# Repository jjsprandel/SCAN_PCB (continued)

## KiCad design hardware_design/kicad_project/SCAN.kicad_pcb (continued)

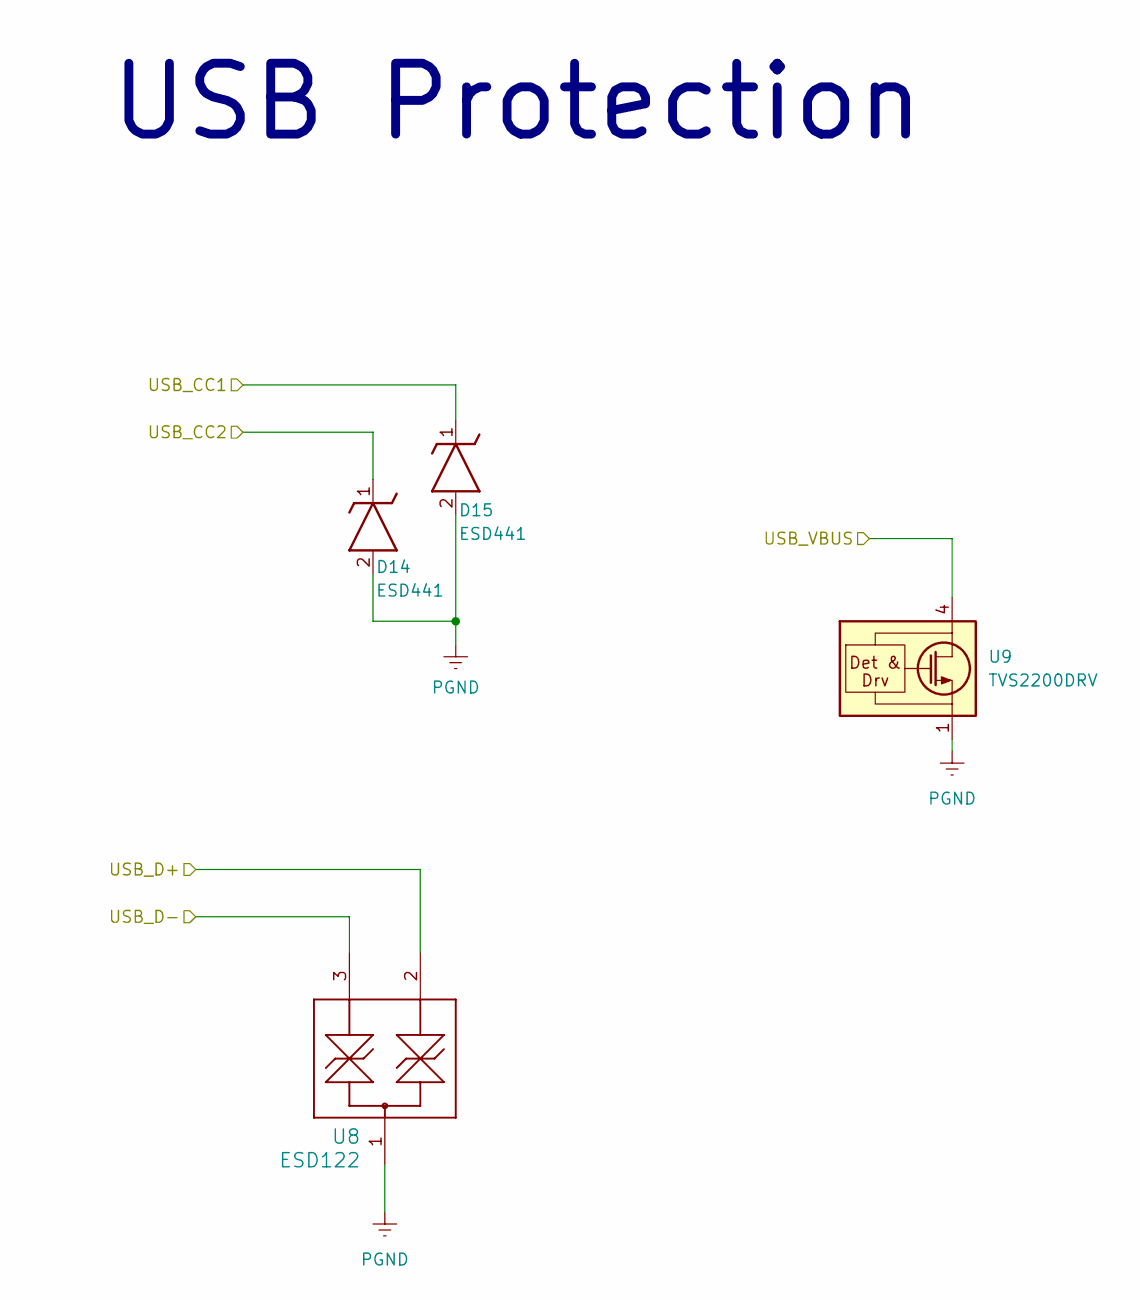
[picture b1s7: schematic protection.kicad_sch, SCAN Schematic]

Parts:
D14, D15: ESD441; X2SON2_DPL_TEX; Manufacturer_Part_Number ESD441DPLR; JLCPCB Part Number C22427765
U8: ESD122; DMY0003A; MFR_PN ESD122DMYR; JLCPCB Part Number C1975871
U9: TVS2200DRV; WSON-6-1EP_2x2mm_P0.65mm_EP1x1.6mm; MFR_PN TVS2200DRVR; JLCPCB Part Number C523793

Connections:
/USB_CC1: D15.1; also elsewhere on the board
/USB_CC2: D14.1; also elsewhere on the board
/USB_D+: U8.2; also elsewhere on the board
/USB_D-: U8.3; also elsewhere on the board
/USB_VBUS: U9.4 (IN), U9.5 (IN), U9.6 (IN); also elsewhere on the board
PGND: D14.2, D15.2, U8.1, U9.1 (GND), U9.2 (GND), U9.3 (GND), U9.7 (GND); also elsewhere on the board

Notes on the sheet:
USB Protection

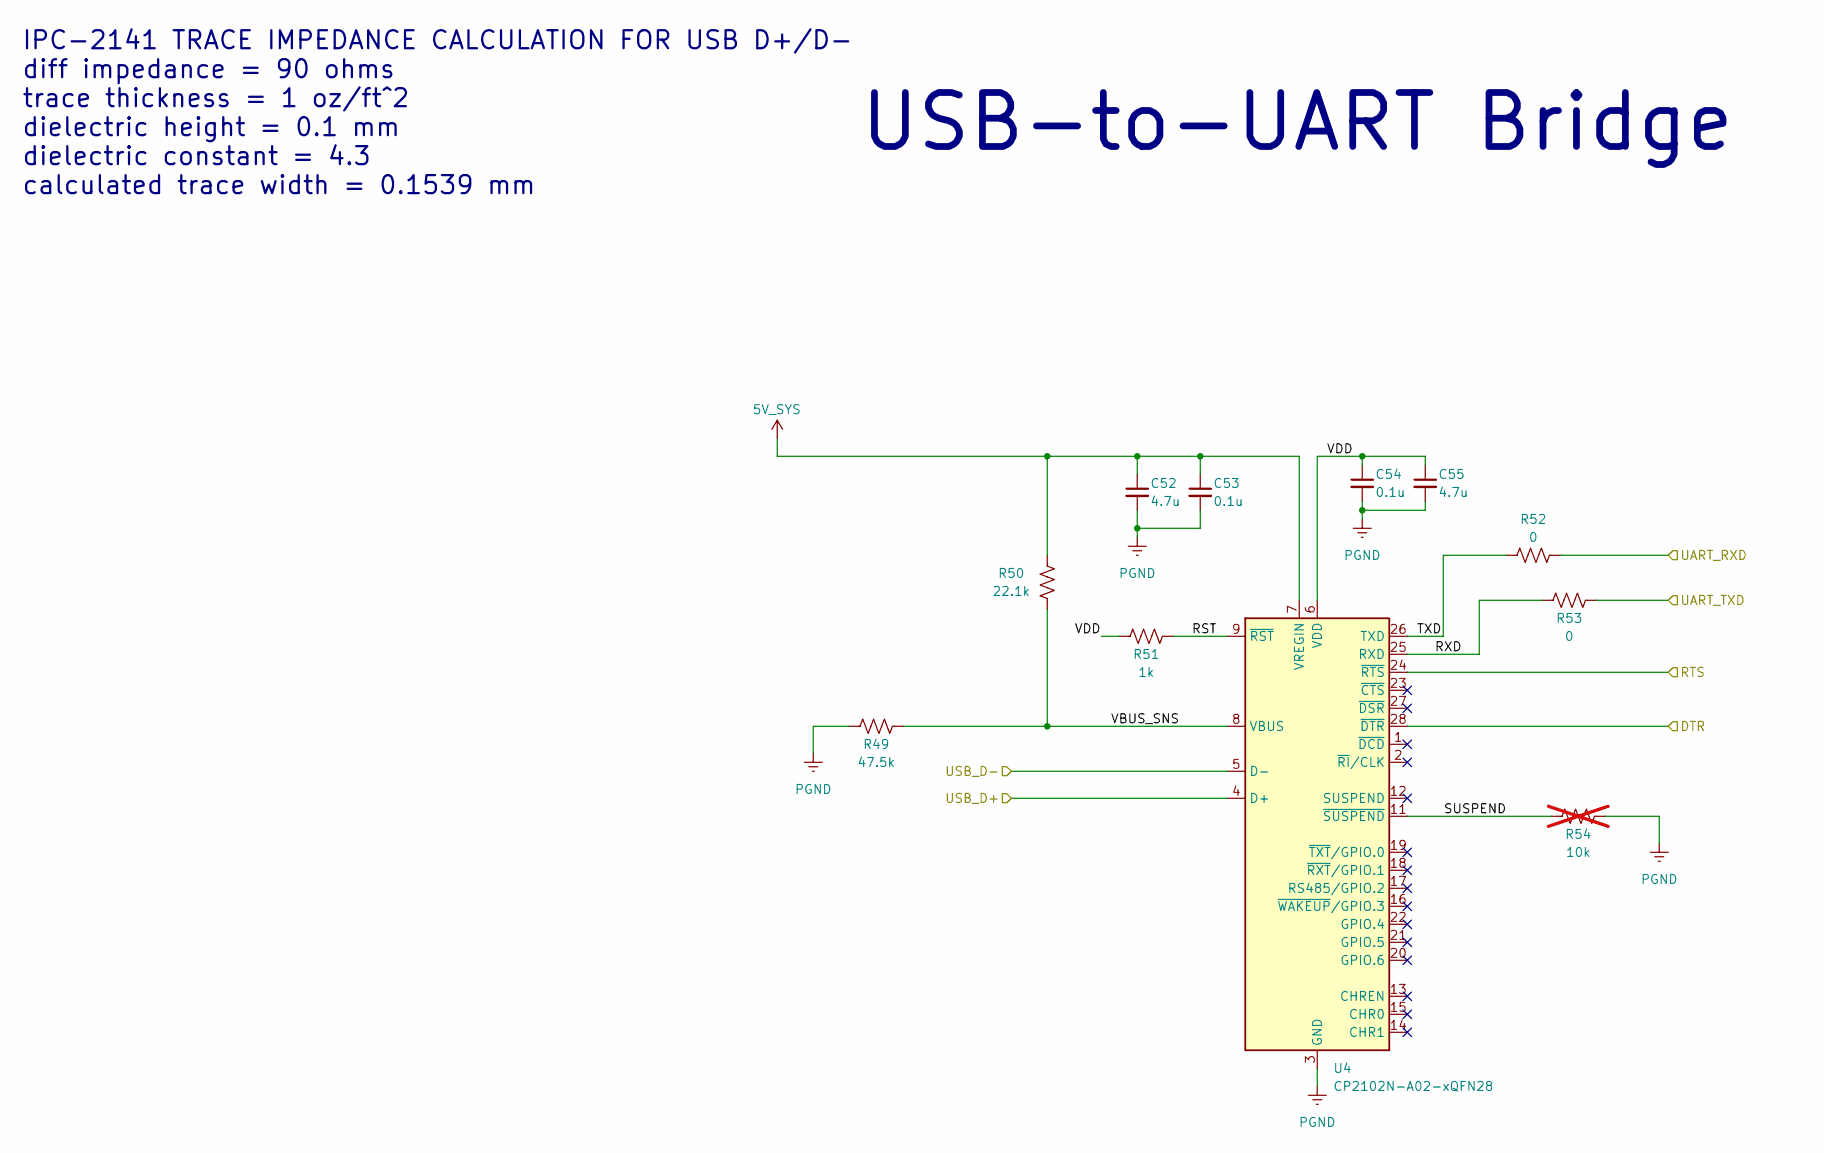
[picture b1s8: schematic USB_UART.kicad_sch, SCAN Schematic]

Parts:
C52, C55: 4.7u; C_0603_1608Metric; MFR_PN GRM188R61C475KAAJD; JLCPCB Part Number C86016
C53, C54: 0.1u; C_0402_1005Metric; MFR_PN GRM155R71A104KA01D; JLCPCB Part Number C71687
R49: 47.5k; R_0402_1005Metric; MFR_PN RC0402FR-0747K5L; JLCPCB Part Number C137974
R50: 22.1k; R_0402_1005Metric; MFR_PN RC0402FR-0722K1L; JLCPCB Part Number C163478
R51: 1k; R_0402_1005Metric; MFR_PN RC0402JR-071KL; JLCPCB Part Number C105637
R52, R53: 0; R_0805_2012Metric; MFR_PN RC0805JR-070RL; JLCPCB Part Number C96345
R54: 10k; R_0805_2012Metric; MFR_PN CRCW080510K0FKEAC; JLCPCB Part Number C844814; not fitted
U4: CP2102N-A02-xQFN28; QFN-28-1EP_5x5mm_P0.5mm_EP3.35x3.35mm; MFR_PN CP2102N-A02-GQFN28; JLCPCB Part Number C1550553

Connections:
5V_SYS: C52.1, C53.1, R50.2, U4.7 (VREGIN); also elsewhere on the board
/Auto Download/DTR: U4.28 (~DTR); also elsewhere on the board
/Auto Download/RTS: U4.24 (~RTS); also elsewhere on the board
/UART_RXD: R52.2; also elsewhere on the board
/UART_TXD: R53.2; also elsewhere on the board
/USB-to-UART Bridge/RST: R51.2, U4.9 (~RST)
/USB-to-UART Bridge/RXD: R53.1, U4.25 (RXD)
/USB-to-UART Bridge/SUSPEND: R54.1, U4.11 (~SUSPEND)
/USB-to-UART Bridge/TXD: R52.1, U4.26 (TXD)
/USB-to-UART Bridge/VBUS_SNS: R49.2, R50.1, U4.8 (VBUS)
/USB-to-UART Bridge/VDD: C54.1, C55.1, R51.1, U4.6 (VDD)
/USB_D+: U4.4 (D+); also elsewhere on the board
/USB_D-: U4.5 (D-); also elsewhere on the board
PGND: C52.2, C53.2, C54.2, C55.2, R49.1, R54.2, U4.3 (GND), U4.29 (GND); also elsewhere on the board

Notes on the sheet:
IPC-2141 TRACE IMPEDANCE CALCULATION FOR USB D+/D- diff impedance = 90 ohms trace thickness = 1 oz/ft^2 dielectric height = 0.1 mm dielectric constant = 4.3 calculated trace width = 0.1539 mm
USB-to-UART Bridge

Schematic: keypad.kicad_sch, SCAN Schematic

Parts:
J8: Keypad; PinHeader_1x08_P2.54mm_Horizontal
R61: 10k; R_0805_2012Metric; MFR_PN CRCW080510K0FKEAC; JLCPCB Part Number C844814
U7: PCF8574; DIP794W45P254L1969H508Q16; MFR_PN PCF8574N; JLCPCB Part Number C2879047

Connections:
3.3V_SYS: R61.1, U7.16 (VDD); also elsewhere on the board
/I2C_SCL: U7.14 (SCL); also elsewhere on the board
/I2C_SDA: U7.15 (SDA); also elsewhere on the board
/KEYPAD_INT: R61.2, U7.13 (~INT); also elsewhere on the board
/Keypad/P0: J8.1, U7.4 (P0)
/Keypad/P1: J8.2, U7.5 (P1)
/Keypad/P2: J8.3, U7.6 (P2)
/Keypad/P3: J8.4, U7.7 (P3)
/Keypad/P4: J8.5, U7.9 (P4)
/Keypad/P5: J8.6, U7.10 (P5)
/Keypad/P6: J8.7, U7.11 (P6)
/Keypad/P7: J8.8, U7.12 (P7)
PGND: U7.1 (A0), U7.2 (A1), U7.3 (A2), U7.8 (VSS); also elsewhere on the board

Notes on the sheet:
Keypad Bus Expander

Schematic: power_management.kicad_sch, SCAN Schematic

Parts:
C4, C5: 1u; C_0805_2012Metric; MFR_PN GRM219R71E105KA88D; JLCPCB Part Number C86035; not fitted
C6: 10u; C_0805_2012Metric; MFR_PN GRM21BR61E106KA73L; JLCPCB Part Number C84416; not fitted
C7, C34, C36, C37: 10u; C_0805_2012Metric_Pad1.18x1.45mm_HandSolder; MFR_PN GRM21BR61E106KA73L; JLCPCB Part Number C84416; not fitted
C8, C9, C23, C24, C26, C27, C29, C30, C32, C35: 10u; C_0805_2012Metric_Pad1.18x1.45mm_HandSolder; MFR_PN GRM21BR61E106KA73L; JLCPCB Part Number C84416
C10, C11, C14, C20, C21: 0.1u; C_0402_1005Metric; MFR_PN GRM155R71H104KE14D; JLCPCB Part Number C77020
C12, C13: 1nF; C_0402_1005Metric; MFR_PN GRM1555C1H102FA01D; JLCPCB Part Number C161523
C15, C16: 0.01u; C_0402_1005Metric; MFR_PN C0402C103J5RACTU; JLCPCB Part Number C2167955; not fitted
C17: 4.7u; C_0603_1608Metric; MFR_PN GRM188R61C475KAAJD; JLCPCB Part Number C86016
C18, C19: 47n; C_0402_1005Metric; MFR_PN GRM155R71E473KA88D; JLCPCB Part Number C77017
C22: 0.1u; C_0402_1005Metric; MFR_PN GRM155R71H104KE14D; JLCPCB Part Number C77020; not fitted
C25, C28: 10u; C_0603_1608Metric; MFR_PN GRT188R61E106ME13D; JLCPCB Part Number C697423
C31: 1n; C_0402_1005Metric; MFR_PN GRM1555C1H102FA01D; JLCPCB Part Number C161523; not fitted
C33: 10u; C_0603_1608Metric; MFR_PN GRT188R61E106ME13D; JLCPCB Part Number C697423; not fitted
C38, C40: 33u; CP_EIA-7343-31_Kemet-D; MFR_PN ECASD41E336M040KA0; JLCPCB Part Number C2161642; not fitted
C39: 33u; CP_EIA-7343-31_Kemet-D; MFR_PN T521D336M035ATE065; JLCPCB Part Number C696815; not fitted
C41: 47nF; C_0402_1005Metric; MFR_PN GRM155R71E473KA88D; JLCPCB Part Number C77017
D1, D2: 12V; D_SOD-523; MFR_PN BZT52C12T-7; JLCPCB Part Number C507911
D3, D4, D6: 40V; D_SOD-523; MFR_PN ZLLS350TA; JLCPCB Part Number C139441; not fitted
D5: GREEN; LED_0603_1608Metric; MFR_PN LTST-C190KGKT; JLCPCB Part Number C125094
D7: 12V; D_SOD-523; MFR_PN BZT52C12T-7; JLCPCB Part Number C507911; not fitted
L1: 1.0u; SPM6530; MFR_PN SPM6530T-1R0M120; JLCPCB Part Number C87572
NT1: NetTie_2; custom_net_tie
Q1, Q2, Q3, Q4: CSD17581Q3A; VSON-8_3.3x3.3mm_P0.65mm_NexFET; MFR_PN CSD17581Q3AT; JLCPCB Part Number C2866708
Q5: CSD17575Q3; VSON-8_3.3x3.3mm_P0.65mm_NexFET; MFR_PN CSD17575Q3T; JLCPCB Part Number C2865030
R5, R6, R21, R22: 0.01; R_2010_5025Metric; MFR_PN WSL2010R0100FEA18; JLCPCB Part Number C844898
R7: 10k; R_0805_2012Metric; MFR_PN CRCW080510K0FKEAC; JLCPCB Part Number C844814
R8, R9, R18: 100k; R_0402_1005Metric; MFR_PN RC0402FR-07100KL; JLCPCB Part Number C60491; not fitted
R10, R11, R19: 0; R_0805_2012Metric; MFR_PN 5106; JLCPCB Part Number C2073530; not fitted
R12: 0; R_0805_2012Metric; MFR_PN RC0805JR-070RL; JLCPCB Part Number C96345
R13, R14: 294; R_0603_1608Metric; MFR_PN RC0603FR-07294RL; JLCPCB Part Number C185345
R15: 18k; R_0603_1608Metric; MFR_PN AC0603FR-0718KL; JLCPCB Part Number C144693
R16: 2.2k; R_0402_1005Metric; MFR_PN RC0402FR-072K21L; JLCPCB Part Number C138019
R17: 0; R_0603_1608Metric; MFR_PN CRCW06030000Z0EA; JLCPCB Part Number C844915
R20: 100; R_0603_1608Metric; MFR_PN RC0603FR-07100RL; JLCPCB Part Number C105588
R23: 5.23k; R_0402_1005Metric; MFR_PN CRCW04025K23FKED; JLCPCB Part Number C2076550
R24: 30.1k; R_0402_1005Metric; MFR_PN RC0402FR-0730K1L; JLCPCB Part Number C138009
RT1: 10k; 103AT2; Mouser Part Number 954-103AT-2
SW1: QON; SW_SPST_PTS647_Sx38; MFR_PN PTS647SM38SMTR2 LFS; DigiKey Part Number PTS647SM38SMTR2LFSCT-ND
U2: BQ25798RQMR; IC_BQ25798RQMR; MFR_PN BQ25798RQMR; JLCPCB Part Number C2876593

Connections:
3.3V_SYS: R7.1, R16.1; also elsewhere on the board
/BAT+: R22.2; also elsewhere on the board
/BQ25798_INT: R7.2, U2.21 (INT_N); also elsewhere on the board
/I2C_SCL: U2.14 (SCL); also elsewhere on the board
/I2C_SDA: U2.15 (SDA); also elsewhere on the board
/PV_IN: R6.1; also elsewhere on the board
/Power Management/ACDRV1: C15.1, D3.1 (K), R13.2, U2.11 (ACDRV1)
/Power Management/ACDRV2: C16.1, D4.1 (K), R14.2, U2.10 (ACDRV2)
/Power Management/BAT: C22.1, C25.1, C28.1, C31.1, C33.1, D7.2 (A), Q5.1 (S), Q5.2 (S), Q5.3 (S), R18.2, R19.1, U2.22 (BAT), U2.23 (BAT)
/Power Management/BATP: C41.1, R20.1, U2.18 (BATP)
/Power Management/BTST1: C18.1, U2.4 (BTST1)
/Power Management/BTST2: C19.1, U2.19 (BTST2)
/Power Management/ILIM_HIZ: R12.1, U2.17 (ILIM_HIZ)
/Power Management/PMID: C20.1, C23.1, C26.1, C30.1, C34.1, C36.1, C38.1, C40.1, U2.29 (PMID)
/Power Management/PROG: R15.2, U2.20 (PROG)
/Power Management/QON: SW1.1, U2.12 (QON_N)
/Power Management/REGN: C17.1, R12.2, R23.1, U2.5 (REGN)
/Power Management/SDRV: D6.1 (K), R17.1, U2.24 (SDRV)
/Power Management/STAT: D5.1 (K), U2.1 (STAT)
/Power Management/SW1: C18.2, L1.1, U2.28 (SW1)
/Power Management/SW2: C19.2, L1.2, U2.26 (SW2)
/Power Management/SYS: C21.1, C24.1, C27.1, C29.1, C32.1, C35.1, C37.1, C39.1, R21.1, U2.25 (SYS)
/Power Management/TS: R23.2, R24.1, RT1.2, U2.16 (TS)
/Power Management/VAC1: C4.1, C11.1, Q1.5 (D), R5.2, R10.1, U2.9 (VAC1)
/Power Management/VAC2: C5.1, C14.1, Q2.5 (D), R6.2, R11.1, U2.8 (VAC2)
/Power Management/VBUS: C6.1, C7.1, C8.1, C9.1, C10.1, Q3.5 (D), Q4.5 (D), R10.2, R11.2, U2.2 (VBUS), U2.3 (VBUS)
/SYSTEM: R21.2; also elsewhere on the board
/VDC: R5.1; also elsewhere on the board
AGND: C11.2, C14.2, C15.2, C16.2, NT1.1, R15.1, R24.2, RT1.1, SW1.2, U2.13 (CE_N)
unnamed: C12.1, D1.2 (A), Q1.1 (S), Q1.2 (S), Q1.3 (S), Q3.1 (S), Q3.2 (S), Q3.3 (S), R8.1
unnamed: C12.2, D1.1 (K), D3.2 (A), Q1.4 (G), Q3.4 (G), R8.2, R13.1
unnamed: C13.1, D2.2 (A), Q2.1 (S), Q2.2 (S), Q2.3 (S), Q4.1 (S), Q4.2 (S), Q4.3 (S), R9.1
unnamed: C13.2, D2.1 (K), D4.2 (A), Q2.4 (G), Q4.4 (G), R9.2, R14.1
unnamed: D5.2 (A), R16.2
unnamed: C31.2, D6.2 (A), D7.1 (K), Q5.4 (G), R17.2, R18.1
unnamed: Q5.5 (D), R19.2, R20.2, R22.1
PGND: C4.2, C5.2, C6.2, C7.2, C8.2, C9.2, C10.2, C17.2, C20.2, C21.2, C22.2, C23.2, C24.2, C25.2, C26.2, C27.2, C28.2, C29.2, C30.2, C32.2, C33.2, C34.2, C35.2, C36.2, C37.2, C38.2, C39.2, C40.2, C41.2, NT1.2, U2.27 (GND); also elsewhere on the board

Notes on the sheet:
At POR and WDT reset... Fsw = 1.5 MHz Battery Cell Count (REG0x0A[7:6]): 4s ICHG (REG0x03/04): 1 A VSYSMIN (REG0x00[5:0]): 12 V VREG (REG0x01/02): 16.8 V VREG Range: 14 V - 18.8 V
Power Management

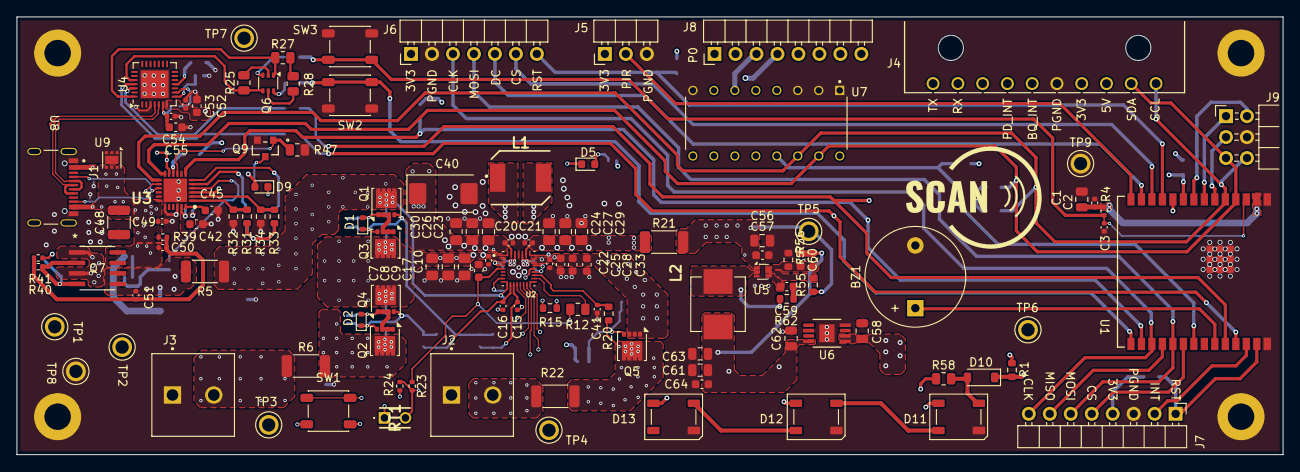
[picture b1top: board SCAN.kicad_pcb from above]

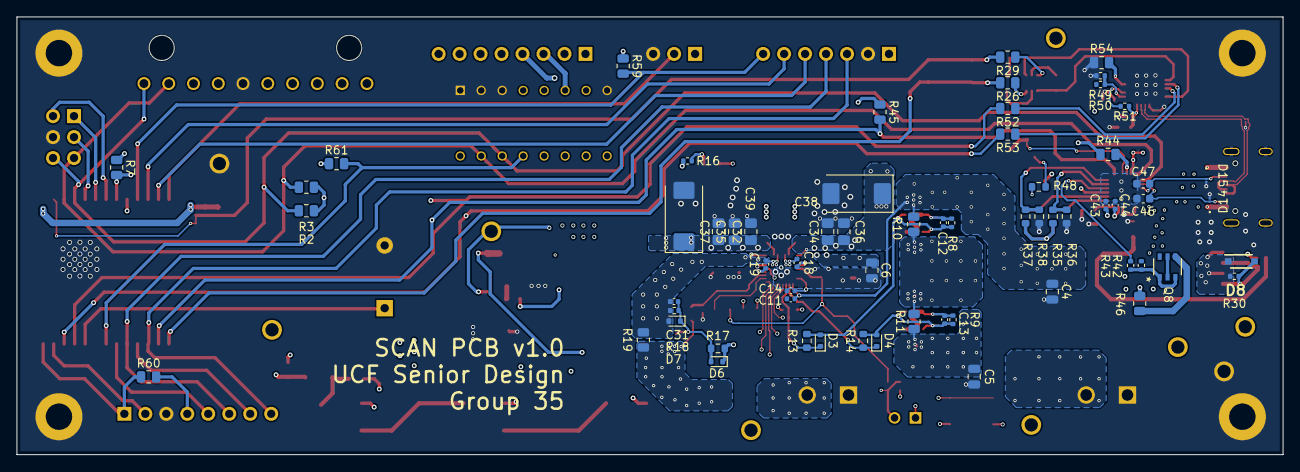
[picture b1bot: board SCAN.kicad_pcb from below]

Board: 6 copper layers, 153.3 x 53.0 mm, 189 parts (64 on the bottom side), 111 nets.

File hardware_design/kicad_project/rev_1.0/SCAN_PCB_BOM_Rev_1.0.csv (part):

"Reference","Value","DNP","Manufacturer_Name","Manufacturer Part Number","JLCPCB Part Number","DigiKey Part Number"
"BZ1","Buzzer","","","","",""
"C1","10u","","Murata Electronics","GRM21BZ71E106KE15L"," C237493",""
"C2","0.1u","","YAGEO","CC0402KRX7R9BB104","C131394",""
"C3","1u","","Murata Electronics","GRM155R61E105KA12D","C77009",""
"C4","1u","DNP","Murata Electronics","GRM219R71E105KA88D","C86035",""
"C5","1u","DNP","Murata Electronics","GRM219R71E105KA88D","C86035",""
"C6","10u","DNP","Murata Electronics","GRM21BR61E106KA73L","C84416",""
"C7","10u","DNP","Murata Electronics","GRM21BR61E106KA73L","C84416",""
"C8","10u","","Murata Electronics","GRM21BR61E106KA73L","C84416",""
"C9","10u","","Murata Electronics","GRM21BR61E106KA73L","C84416",""
"C10","0.1u","","Murata Electronics","GRM155R71H104KE14D","C77020",""
"C11","0.1u","","Murata Electronics","GRM155R71H104KE14D","C77020",""
"C12","1nF","","Murata Electronics","GRM1555C1H102FA01D","C161523",""
"C13","1nF","","Murata Electronics","GRM1555C1H102FA01D","C161523",""
"C14","0.1u","","Murata Electronics","GRM155R71H104KE14D","C77020",""
"C15","0.01u","DNP","KEMET","C0402C103J5RACTU","C2167955",""
"C16","0.01u","DNP","KEMET","C0402C103J5RACTU","C2167955",""
"C17","4.7u","","Murata Electronics","GRM188R61C475KAAJD","C86016",""
"C18","47n","","Murata Electronics","GRM155R71E473KA88D","C77017",""
"C19","47n","","Murata Electronics","GRM155R71E473KA88D","C77017",""
"C20","0.1u","","Murata Electronics","GRM155R71H104KE14D","C77020",""
"C21","0.1u","","Murata Electronics","GRM155R71H104KE14D","C77020",""
"C22","0.1u","DNP","Murata Electronics","GRM155R71H104KE14D","C77020",""
"C23","10u","","Murata Electronics","GRM21BR61E106KA73L","C84416",""
"C24","10u","","Murata Electronics","GRM21BR61E106KA73L","C84416",""
"C25","10u","","Murata Electronics","GRT188R61E106ME13D","C697423",""
"C26","10u","","Murata Electronics","GRM21BR61E106KA73L","C84416",""
"C27","10u","","Murata Electronics","GRM21BR61E106KA73L","C84416",""
"C28","10u","","Murata Electronics","GRT188R61E106ME13D","C697423",""
"C29","10u","","Murata Electronics","GRM21BR61E106KA73L","C84416",""
"C30","10u","","Murata Electronics","GRM21BR61E106KA73L","C84416",""
"C31","1n","DNP","Murata Electronics","GRM1555C1H102FA01D","C161523",""
"C32","10u","","Murata Electronics","GRM21BR61E106KA73L","C84416",""
"C33","10u","DNP","Murata Electronics","GRT188R61E106ME13D","C697423",""
"C34","10u","DNP","Murata Electronics","GRM21BR61E106KA73L","C84416",""
"C35","10u","","Murata Electronics","GRM21BR61E106KA73L","C84416",""
"C36","10u","DNP","Murata Electronics","GRM21BR61E106KA73L","C84416",""
"C37","10u","DNP","Murata Electronics","GRM21BR61E106KA73L","C84416",""
"C38","33u","DNP","Murata Electronics","ECASD41E336M040KA0","C2161642",""
"C39","33u","DNP","KEMET","T521D336M035ATE065","C696815",""
"C40","33u","DNP","Murata Electronics","ECASD41E336M040KA0","C2161642",""
"C41","47nF","","Murata Electronics","GRM155R71E473KA88D","C77017",""
"C42","1u","","Murata Electronics","GCM188R71C105KA64D","C161212",""
"C43","0.1u","","Murata Electronics","GRM155R71A104KA01D","C71687",""
"C44","0.1u","","Murata Electronics","GRM155R71A104KA01D","C71687",""
"C45","1u","","Murata Electronics","GCM188R71C105KA64D","C161212",""
"C46","390p","","YAGEO","CC0603JRX7R9BB391","C519518",""
"C47","390p","","YAGEO","CC0603JRX7R9BB391","C519518",""
"C48","3.3u","","Murata Electronics","GRM32DR71H335KA88L","C397310",""
"C49","100n","","Taiyo Yuden","GMK105BJ104KV-F","C187828",""
"C50","1u","","Samsung Electro-Mechanics","CL05A105KL5NRNC","C307413",""
"C51","1u","DNP","TDK Corporation","C1005X5R1V105K050BC","","445-9073-1-ND"
"C52","4.7u","","Murata Electronics","GRM188R61C475KAAJD","C86016",""
"C53","0.1u","","Murata Electronics","GRM155R71A104KA01D","C71687",""
"C54","0.1u","","Murata Electronics","GRM155R71A104KA01D","C71687",""
"C55","4.7u","","Murata Electronics","GRM188R61C475KAAJD","C86016",""
"C56","10u","","Murata Electronics","GRM21BR61E106MA73L","C391262",""
"C57","0.1u","","YAGEO","CC0603KRX7R9BB104","C14663",""
"C58","2.2u","","YAGEO","CC0805KKX7R9BB225","C125847",""
"C59","0.1u","","YAGEO","CC0603KRX7R9BB104","C14663",""
"C60","18p","DNP","","","",""
"C61","22u","","Murata Electronics","GRM21BR61A226ME44L","C441864",""
"C62","1u","","YAGEO","CC0805KKX7R9BB105","C91185",""
"C63","22u","","Murata Electronics","GRM21BR61A226ME44L","C441864",""
"C64","0.1u","","YAGEO","CC0603KRX7R9BB104","C14663",""
"D1","12V","","Diodes Incorporated","BZT52C12T-7","C507911",""
"D2","12V","","Diodes Incorporated","BZT52C12T-7","C507911",""
"D3","40V","DNP","Diodes Incorporated","ZLLS350TA","C139441",""
"D4","40V","DNP","Diodes Incorporated","ZLLS350TA","C139441",""
"D5","GREEN","","Lite-On Inc.","LTST-C190KGKT","C125094",""
"D6","40V","DNP","Diodes Incorporated","ZLLS350TA","C139441",""
"D7","12V","DNP","Diodes Incorporated","BZT52C12T-7","C507911",""
"D8","NZH10C-115","","Nexperia USA Inc.","NZH10C,115","C551630",""
"D9","RED","","Lite-On Inc.","LTST-C190EKT ","C364560",""
"D10","1N4148W","","Jiangsu Changjing Electronics Technology Co., Ltd.","1N4448W","C8601",""
"D11","WS2812B","","SparkFun Electronics"," COM-16347","C7433145",""
"D12","WS2812B","","SparkFun Electronics"," COM-16347","C7433145",""
"D13","WS2812B","","SparkFun Electronics"," COM-16347","C7433145",""
"D14","ESD441","","Texas Instruments","ESD441DPLR","C22427765",""
"D15","ESD441","","Texas Instruments","ESD441DPLR","C22427765",""
"J1","USB_C_16P_Connector","","Korean Hroparts Elec","TYPE-C-31-M-12","C165948",""
"J2","Batt_Connector","","Ningbo Kangnex Elec","WJ128V-5.0-2P","C8269","A98355-ND"
"J3","PV_Panel_Connector","","Ningbo Kangnex Elec","WJ128V-5.0-2P","C8269","A98355-ND"
"J4","Conn_01x10","","Molex","0436501000","","23-0436501000-ND"
"J5","PIR_CONNECTOR","","CJT(Changjiang Connectors)","A2541WR-3P","C225489",""
"J6","TFT_CONN","","","","",""
"J7","PN532_CONN","","","","",""
"J8","Keypad","","","","",""
"J9","GPIO_BREAKOUT","","","","",""
"L1","1.0u","","TDK Corporation","SPM6530T-1R0M120","C87572",""
"L2","4.7u","","Würth Elektronik","74437349047","C6404631","732-3354-1-ND"
"Q1","CSD17581Q3A","","Texas Instruments","CSD17581Q3AT","C2866708",""
"Q2","CSD17581Q3A","","Texas Instruments","CSD17581Q3AT","C2866708",""
"Q3","CSD17581Q3A","","Texas Instruments","CSD17581Q3AT","C2866708",""
"Q4","CSD17581Q3A","","Texas Instruments","CSD17581Q3AT","C2866708",""
"Q5","CSD17575Q3","","Texas Instruments","CSD17575Q3T","C2865030",""
"Q6","BC847BDW1","","onsemi","BC847BDW1T1G","C82368",""
"Q7","IRF9358TRPBF","","Infineon Technologies","IRF9358TRPBF","C537847",""
"Q8","BSL308PE","","","","",""
"Q9","NTR4503NT1G","","onsemi","NTR4503NT1G","C94763",""
"R1","3.3k","","","","",""
"R2","2.2k","","","","",""
"R3","2.2k","","","","",""
"R4","10k","","","","",""
"R5","0.01","","Vishay Dale","WSL2010R0100FEA18","C844898",""
"R6","0.01","","Vishay Dale","WSL2010R0100FEA18","C844898",""
"R7","10k","","","","",""
"R8","100k","DNP","YAGEO","RC0402FR-07100KL","C60491",""
"R9","100k","DNP","YAGEO","RC0402FR-07100KL","C60491",""
"R10","0","DNP","","","",""
"R11","0","DNP","","","",""
"R12","0","","","","",""
"R13","294","","YAGEO","RC0603FR-07294RL","C185345",""
"R14","294","","YAGEO","RC0603FR-07294RL","C185345",""
"R15","17.4k","","","","",""
"R16","2.2k","","","","",""
"R17","0","","Vishay Dale","CRCW06030000Z0EA","C844915",""
"R18","100k","DNP","","","",""
"R19","0","DNP","Keystone Electronics","5106","C2073530","36-5106CT-ND"
"R20","100","","YAGEO","RC0603FR-07100RL","C105588",""
"R21","0.01","","Vishay Dale","WSL2010R0100FEA18","C844898",""
"R22","0.01","","Vishay Dale","WSL2010R0100FEA18","C844898",""
"R23","5.23k","","Vishay Dale","CRCW04025K23FKED","C2076550",""
"R24","30.1k","","YAGEO","RC0402FR-0730K1L","C138009",""
"R25","10k","","","","",""
"R26","0","","","","",""
"R27","10k","","","","",""
"R28","0","","","","",""
"R29","0","","","","",""
"R30","49.9k","","KOA Speer Electronics, Inc.","RK73H1ETTP4992F","C173335",""
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
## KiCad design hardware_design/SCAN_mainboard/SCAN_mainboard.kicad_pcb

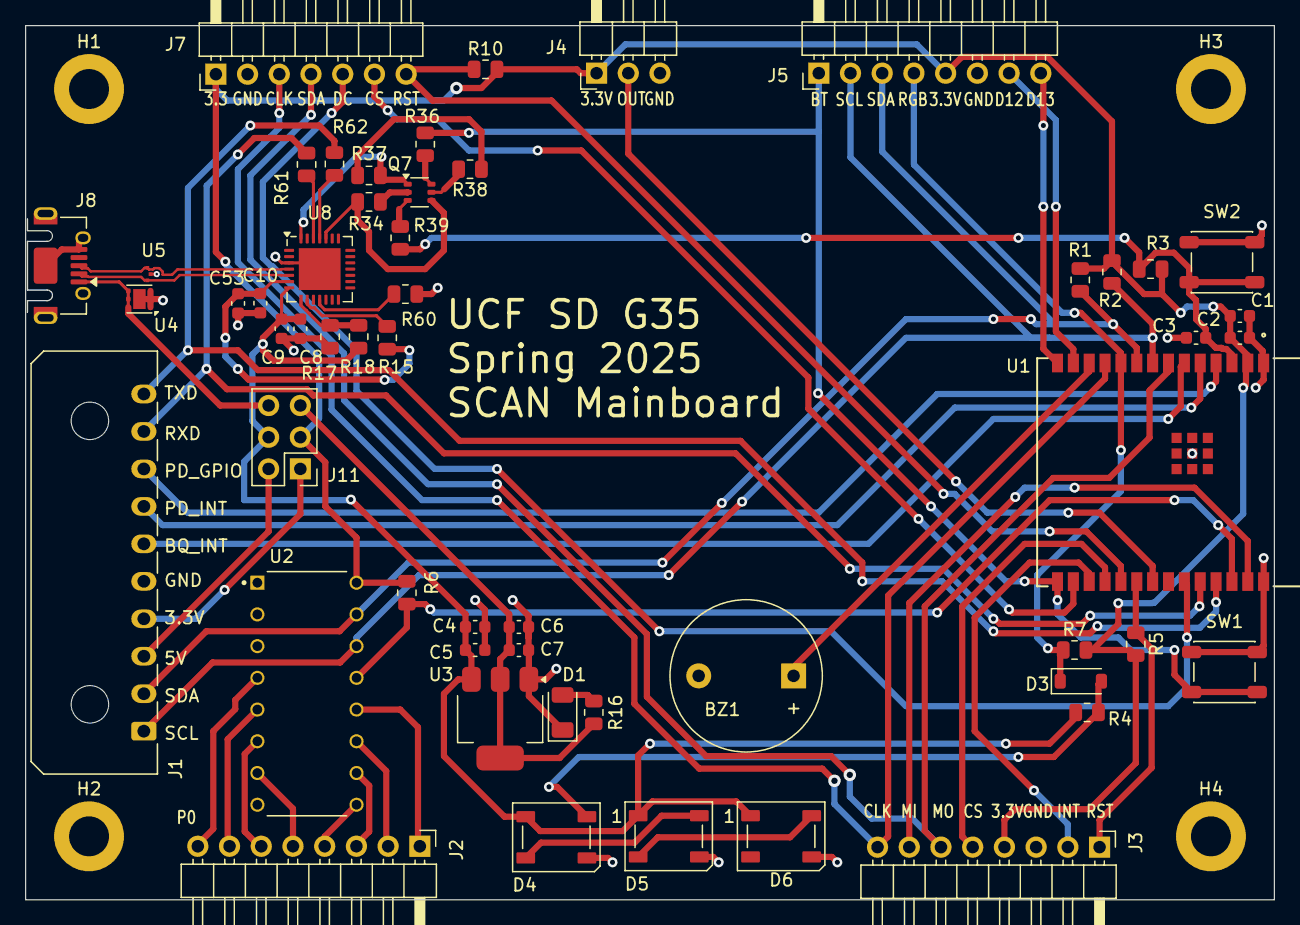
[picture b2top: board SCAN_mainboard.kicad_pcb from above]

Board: 2 copper layers, 100.0 x 70.0 mm, 58 parts (0 on the bottom side), 58 nets.

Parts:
BZ1: Buzzer; Buzzer_12x9.5RM7.6
C1: 10u; C_0603_1608Metric
C2: 0.1u; C_0603_1608Metric
C3: 1u; C_0603_1608Metric
C4, C6: 10uF; C_0603_1608Metric
C5, C7: 100nF; C_0603_1608Metric
C8, C53: .1u; C_0603_1608Metric
C9, C10: 4.7u; C_0603_1608Metric
D1: LED; LED_1206_3216Metric
D3: 1N4148W; D_SOD-123
D4: SUCCESS_LED; LED_WS2812B_PLCC4_5.0x5.0mm_P3.2mm
D5: FAILURE_LED; LED_WS2812B_PLCC4_5.0x5.0mm_P3.2mm
D6: ADMIN_LED; LED_WS2812B_PLCC4_5.0x5.0mm_P3.2mm
H1, H2, H3, H4: MountingHole_Pad; MountingHole_3.2mm_M3_DIN965_Pad
J1: Conn_01x10; Molex_Micro-Fit_3.0_43650-1000_1x10_P3.00mm_Horizontal
J2: KEYPAD_CONN; PinHeader_1x08_P2.54mm_Horizontal
J3: PN532_CONN; PinHeader_1x08_P2.54mm_Horizontal
J4: PIR_CONN; PinHeader_1x03_P2.54mm_Horizontal
J5: DEBUG_BREAKOUT; PinHeader_1x08_P2.54mm_Horizontal
J7: TFT_CONN; PinHeader_1x07_P2.54mm_Horizontal
J8: USB_B_Micro; USB_Micro-AB_Molex_47590-0001
J11: PWR_MUX; PinHeader_2x03_P2.54mm_Vertical
Q7: BC847BDW1; SOT-363_SC-70-6
R1, R2: 2.2k; R_0805_2012Metric
R3, R4, R5, R6, R10, R34, R37: 10k; R_0805_2012Metric
R7: 3.3k; R_0805_2012Metric
R15: 1k; R_0805_2012Metric
R16: 120; R_0805_2012Metric
R17: 47.5k; R_0805_2012Metric
R18: 22.1k; R_0805_2012Metric
R36, R38, R39, R60, R61, R62: 0Ω; R_0805_2012Metric
SW1: RST_SWITCH; SW_SPST_PTS647_Sx38
SW2: SW_Push; SW_SPST_PTS647_Sx38
U1: ESP32-C6-WROOM-1-N8
U2: PCF8574; DIP794W45P254L1969H508Q16
U3: AMS1117-3.3; SOT-223-3_TabPin2
U4: TVS2200DRV; WSON-6-1EP_2x2mm_P0.65mm_EP1x1.6mm
U5: ESD122DMYR; DMY0003A
U8: CP2102N-A02-xQFN28; QFN-28-1EP_5x5mm_P0.5mm_EP3.35x3.35mm

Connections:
3.3V_LDO_OUT: C6.1, C7.1, J11.3, R16.1, U3.2 (VO)
3.3V_PWR_BRD: J1.4, J11.1
3.3V_SYS: C1.1, C2.1, J3.4, J4.1, J5.5, J7.1, J11.2, R1.1, R2.1, R3.1, R5.2, R6.1, R7.2, R10.2, U1.2 (3V3), U2.16 (VDD)
5V_PWR_BRD: J1.3, J11.4
5V_SYS: C4.1, C5.1, C8.1, C9.1, D4.1 (VDD), D5.1 (VDD), D6.1 (VDD), J11.5, R4.1, R18.2, U3.3 (VI), U8.7 (VREGIN)
/Auto Download/DTR: Q7.1 (E1), R37.1, U8.28 (~DTR)
/Auto Download/RTS: Q7.4 (E2), R34.1, U8.24 (~RTS)
/BOOT: J5.1, R36.2, SW1.2, U1.15 (GPIO9)
/BQ25798_INT: J1.6, U1.6 (GPIO6)
/BUZZER_PWM: BZ1.1 (+), U1.12 (GPIO11)
/CHIP_PU: C3.1, R3.2, R39.2, SW2.2, U1.3 (EN)
/GPIO12_BREAKOUT: J5.7, U1.13 (GPIO12)
/GPIO13_BREAKOUT: J5.8, U1.14 (GPIO13)
/I2C_SCL: J1.1, J5.2, R2.2, U1.8 (GPIO0), U2.14 (SCL)
/I2C_SDA: J1.2, J5.3, R1.2, U1.9 (GPIO1), U2.15 (SDA)
/KEYPAD_INT: R6.2, U1.26 (GPIO3), U2.13 (~INT)
/MICRO_USB_D+: J8.3 (D+), U5.2, U8.4 (D+)
/MICRO_USB_D-: J8.2 (D-), U5.3, U8.5 (D-)
/NFC_INT: J3.2, U1.17 (GPIO19)
/NFC_RST: J3.1, R5.1, U1.20 (GPIO22)
/P0: J2.8, U2.4 (P0)
/P1: J2.7, U2.5 (P1)
/P2: J2.6, U2.6 (P2)
/P3: J2.5, U2.7 (P3)
/P4: J2.4, U2.9 (P4)
/P5: J2.3, U2.10 (P5)
/P6: J2.2, U2.11 (P6)
/P7: J2.1, U2.12 (P7)
/PD_GPIO: J1.8, U1.4 (GPIO4)
/PD_INT: J1.7, U1.5 (GPIO5)
/PIR_OUT: J4.2, U1.21 (GPIO23)
/RGB_1: D3.2 (A), D4.4 (DIN), R4.2
/RGB_12: D4.2 (DOUT), D5.4 (DIN)
/RGB_23: D5.2 (DOUT), D6.4 (DIN)
/RGB_CTRL: D3.1 (K), J5.4, R7.1, U1.10 (GPIO8)
/SPI_CLK: J3.8, J7.3, U1.11 (GPIO10)
/SPI_CS: J3.5, U1.18 (GPIO20)
/SPI_MISO: J3.7, U1.27 (GPIO2)
/SPI_MOSI: J3.6, J7.4, U1.7 (GPIO7)
/TFT_CS: J7.6, U1.16 (GPIO18)
/TFT_DC: J7.5, U1.23 (GPIO15)
/TFT_RESET_N: J7.7, R10.1, U1.19 (GPIO21)
/UART_RXD: J1.9, R61.2, U1.24 (GPIO17)
/UART_TXD: J1.10, R62.2, U1.25 (GPIO16)
/USB-to-UART Bridge/RST: R15.2, U8.9 (~RST)
/USB-to-UART Bridge/RXD: R62.1, U8.25 (RXD)
/USB-to-UART Bridge/SUSPEND: R60.1, U8.11 (~SUSPEND)
/USB-to-UART Bridge/TXD: R61.1, U8.26 (TXD)
/USB-to-UART Bridge/VBUS_SNS: R17.2, R18.1, U8.8 (VBUS)
/USB-to-UART Bridge/VDD: C10.1, C53.1, R15.1, U8.6 (VDD)
AGND: BZ1.2 (-), C1.2, C2.2, C3.2, C4.2, C5.2, C6.2, C7.2, C8.2, C9.2, C10.2, C53.2, D1.1 (K), D4.3 (VSS), D5.3 (VSS), D6.3 (VSS), H1.1, H2.1, H3.1, H4.1, J1.5, J3.3, J4.3, J5.6, J7.2, J8.5 (GND), J8.6 (Shield), R17.1, R60.2, SW1.1, SW2.1, U1.1 (GND), U1.28 (GND), U1.29 (GND), U2.1 (A0), U2.2 (A1), U2.3 (A2), U2.8 (VSS), U3.1 (GND), U4.1 (GND), U4.2 (GND), U4.3 (GND), U4.7 (GND), U5.1, U8.3 (GND), U8.29 (GND)
unnamed: D1.2 (A), R16.2
unnamed: Q7.2 (B1), R34.2
unnamed: Q7.6 (C1), R36.1
unnamed: Q7.5 (B2), R38.2
unnamed: Q7.3 (C2), R39.1
unnamed: R37.2, R38.1
VBUS: J8.1 (VBUS), J11.6, U4.4 (IN), U4.5 (IN), U4.6 (IN)

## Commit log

2025-02-15 finished routing SCAN mainboard. Flagged for Dre review
2025-02-16 final commit before ordering mainboard rev1
2025-02-21 PCB work. Things to still do: 1. Add breakout pins for I2C/SPI/3V3 2. Connect AGND to PGND under BQ25798 3. Add copper fill for AGND 4. finish routing signals to ESP32 5. Check trace and via clearanc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
2025-02-21 backup files only
2025-02-24 reorganized schematic for CDR presentation
2025-02-25 Fixed peripherals PCB connector pinout Finished routing all but 5V Need to double check 5V regulator and 3.3V LDO layout 16 missing connections on DRC, no violations
2025-02-25 Changes: 1. Added datasheets and reference designs 2. Cleaned up folder structure
    To do:
    1. Replace USB4110-GF-A_GCT USB-C connector with
    TYPE-C-31-M-12 connector
    2. Fix DRC errors
    3. Add breakout pins for extra ESP32 pins
    4. Confirm buzzer schematic
2025-02-26 more changes
2025-02-27 hardware changes
2025-02-28 Dre updates to firebase firmware for json parsing and acitivityLog updates (#64)
    * included cJSON library and successfully read back and parsed a database user node
    * Firebase check-in function now reads user node json and sends a json ndoe to the activity log to check in users. need to add timestamp functionality
    * check_in_user_task now manages user check in and check out events, posting a new activity log event to the database with the proper fields - fully functional - may need some cleaning
2025-02-28 Complete: 1. Replaced USB C connector 2. BOM in progress 3. Fixed some errors
    To Do:
    1. Finish BOM
    2. Connect 5V
    3. Double check layout
    4. Remove any violations/errors
2025-02-28 Added Dre as codeowner for JSON parsing files
2025-03-01 custom footprint for net tie on inner layer made by using text editor to manually put footprint on In2.Cu layer
2025-03-02 Completed: 1. BOM progress 2. rerouted 5V buck converter and 3V3 LDO 3. Fixed some DRC violations
    To do:
    1. Finish BOM
2025-03-03 BOM finished, need to fix a few violations and then ready to order
2025-03-03 updated firebase firmware to reflect changes to database user field types
2025-03-04 working up until CREATE_NO_WINDOW
2025-03-05 weird schematic error fixed
2025-03-05 trying to fix again
2025-03-05 trying to fix file error again
2025-03-05 first test for flashing from macbook
2025-03-05 small fix to import python modules after they are actually downloaded with pip
2025-03-06 Minor comitt to fix str cmp I forgot to push
2025-03-07 Fix for flashing from windows
2025-03-07 Added NDEF component
2025-03-07 fixing build errors (#71)
2025-03-07 build fix part 2 (#72)
2025-03-08 State machine modification (#73)
    * added additional states to state machine and integrated NFC transciever
    * Changed length of NFC ID due to updated Firebase
    IDs
    ---------
2025-03-08 kicad_project changes
2025-03-08 new commit because hardware design diverged as I switched branches
2025-03-09 hardware backups
2025-03-10 removing software files
2025-03-13 second revision of SCAN_PCB
